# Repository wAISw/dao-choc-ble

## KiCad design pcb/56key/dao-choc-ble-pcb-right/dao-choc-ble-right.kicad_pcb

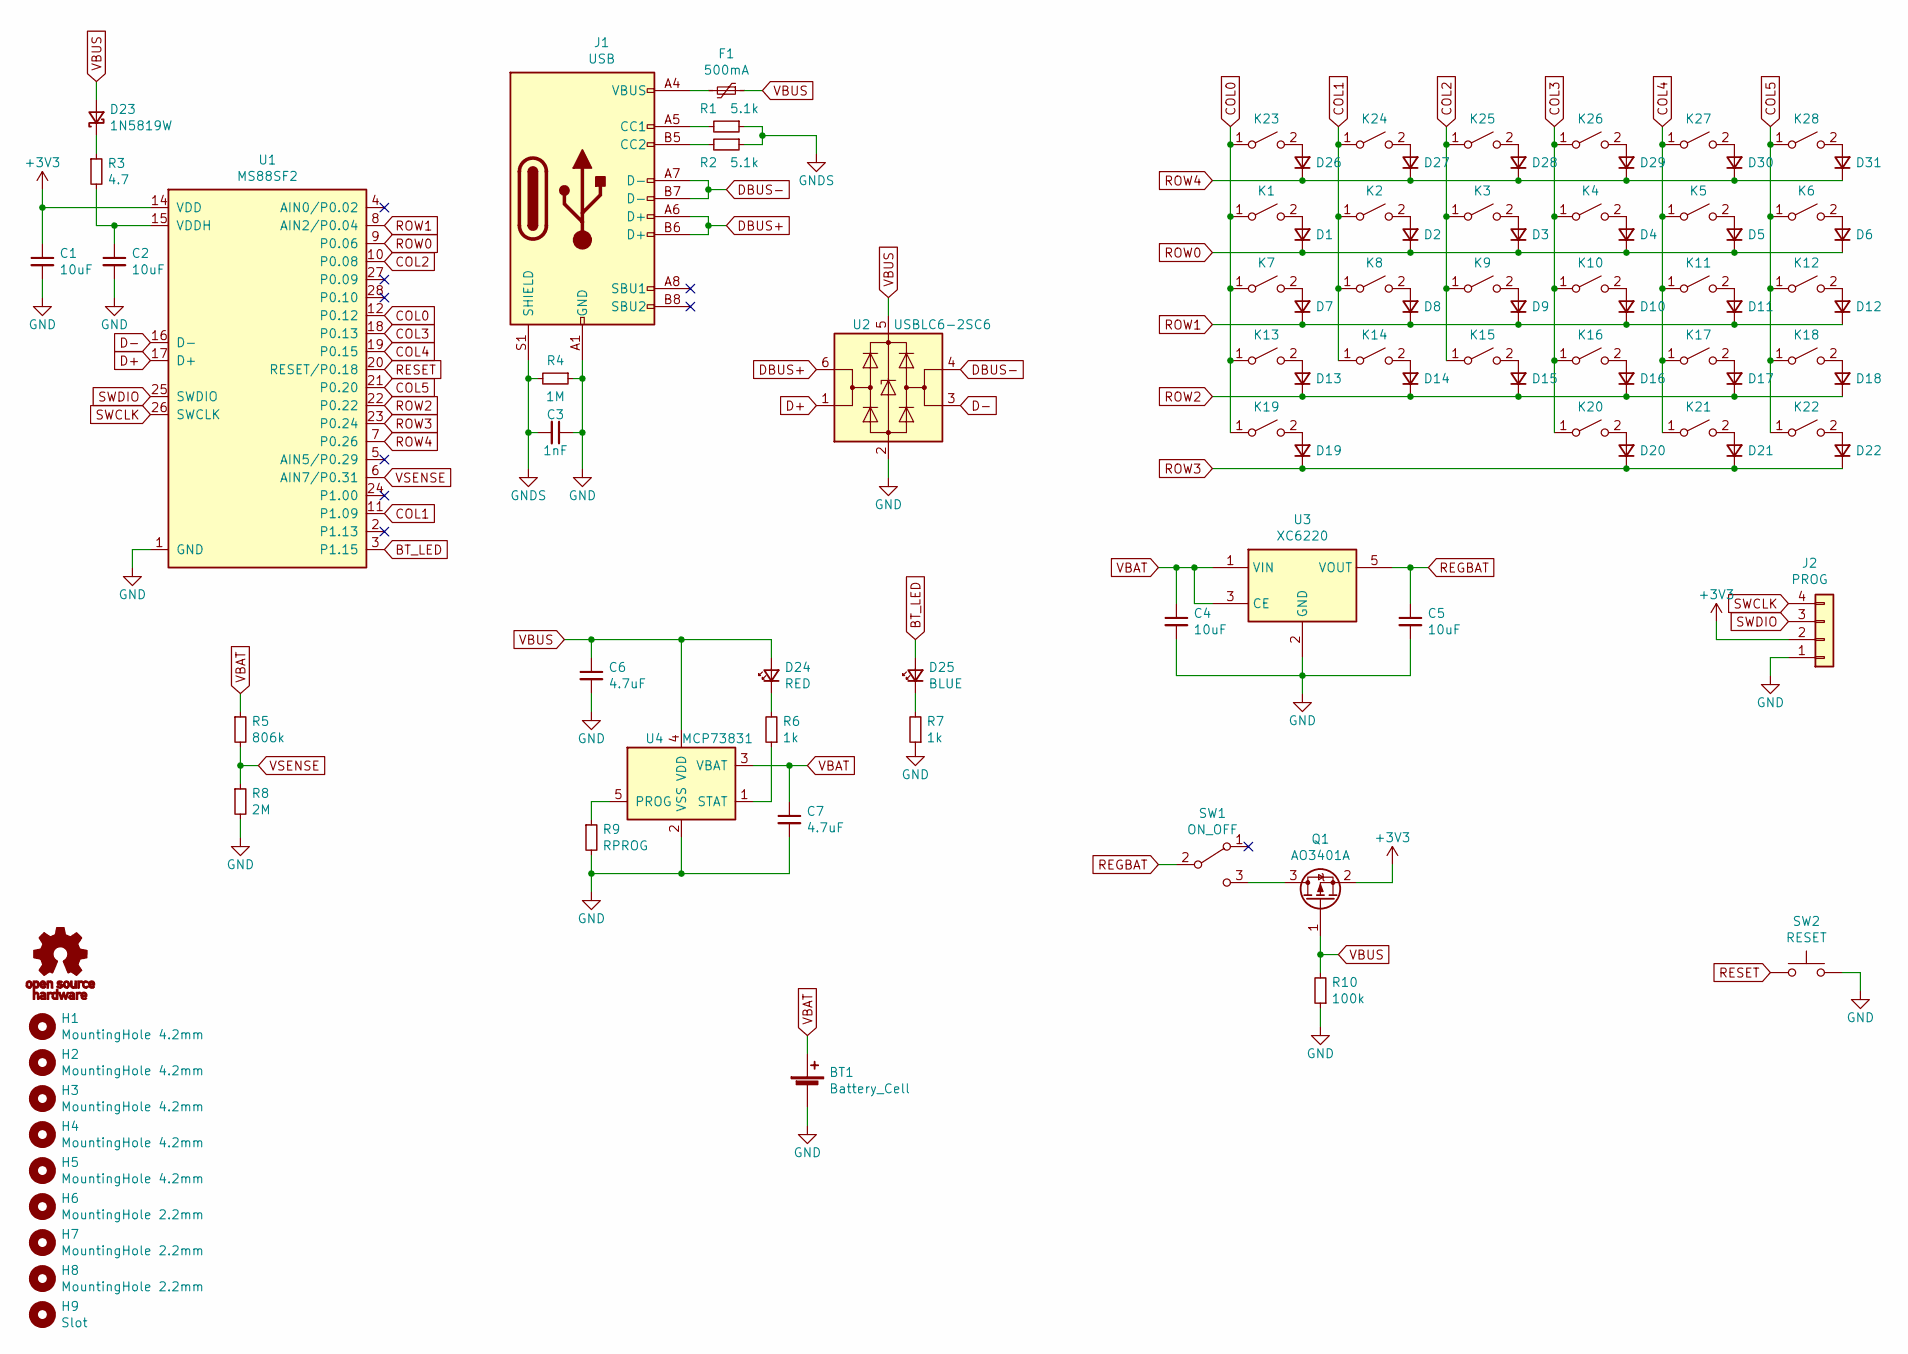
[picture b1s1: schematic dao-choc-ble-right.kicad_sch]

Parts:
BT1: Battery_Cell; Battery
C1, C2, C4, C5: 10uF; C_0603_1608Metric; LCSC C19702
C3: 1nF; C_0603_1608Metric; LCSC C1588
C6, C7: 4.7uF; C_0603_1608Metric; LCSC C19666
D1, D2, D3, D4, D5, D6, D7, D8, D9, D10, D11, D12, D13, D14, D15, D16, D17, D18, D19, D20, D21, D22, D26, D27, D28, D29, D30, D31: 1N4148WS; D_SOD-323; LCSC C57759
D23: 1N5819W; D_SOD-123; LCSC C169540
D24: RED; LED_0603_1608Metric; LCSC C2286
D25: BLUE; LED_0603_1608Metric; LCSC C72041
F1: 500mA; Fuse_1206_3216Metric; LCSC C355568
H1, H2, H3, H4, H5: MountingHole 4.2mm; Hole_4.2mm
H6, H7, H8: MountingHole 2.2mm; Hole_2.2mm
H9: Slot
J1: USB; USB-C_C168688; LCSC C168688
J2: PROG
K1, K2, K3, K4, K5, K6, K7, K8, K9, K10, K11, K12, K13, K14, K15, K16, K17, K18, K19, K20, K21, K22, K23, K24, K25, K26, K27, K28: KEY_SWITCH; Kailh_PG1350_hotswap
LOGO1: OSHW-logo
Q1: AO3401A; SOT-23; LCSC C15127
R1, R2: 5.1k; R_0603_1608Metric; LCSC C23186
R3: 4.7; R_0603_1608Metric; LCSC C23164
R4: 1M; R_0603_1608Metric; LCSC C22935
R5: 806k; R_0603_1608Metric; LCSC C103828
R6, R7: 1k; R_0603_1608Metric; LCSC C21190
R8: 2M; R_0603_1608Metric; LCSC C22976
R9: RPROG; R_0603_1608Metric; LCSC C22978
R10: 100k; R_0603_1608Metric; LCSC C25803
SW1: ON_OFF; MSK-12C02; LCSC C431541
SW2: RESET; TS-1086E; LCSC C455276
U1: MS88SF2; MINEW_MS88SF2
U2: USBLC6-2SC6; SOT-23-6; LCSC C558442
U3: XC6220; SOT-23-5; LCSC C86534
U4: MCP73831; SOT-23-5; LCSC C14879

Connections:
+3V3: C1.1, J2.2, Q1.2 (S), U1.14 (VDD)
BT_LED: D25.2 (A), U1.3 (P1.15)
COL0: K1.1 (A), K7.1 (A), K13.1 (A), K19.1 (A), K23.1 (A), U1.12 (P0.12)
COL1: K2.1 (A), K8.1 (A), K14.1 (A), K24.1 (A), U1.11 (P1.09)
COL2: K3.1 (A), K9.1 (A), K15.1 (A), K25.1 (A), U1.10 (P0.08)
COL3: K4.1 (A), K10.1 (A), K16.1 (A), K20.1 (A), K26.1 (A), U1.18 (P0.13)
COL4: K5.1 (A), K11.1 (A), K17.1 (A), K21.1 (A), K27.1 (A), U1.19 (P0.15)
COL5: K6.1 (A), K12.1 (A), K18.1 (A), K22.1 (A), K28.1 (A), U1.21 (P0.20)
D+: U1.17 (D+), U2.1 (I/O1)
D-: U1.16 (D-), U2.3 (I/O2)
DBUS+: J1.A6 (D+), J1.B6 (D+), U2.6 (I/O1)
DBUS-: J1.A7 (D-), J1.B7 (D-), U2.4 (I/O2)
GND: BT1.2 (-), C1.2, C2.2, C3.1, C4.2, C5.2, C6.2, C7.2, J1.A1 (GND), J1.A12 (GND), J1.B1 (GND), J1.B12 (GND), J2.1, R4.1, R7.1, R8.2, R9.2, R10.1, SW2.2, U1.1 (GND), U1.13 (GND), U2.2 (GND), U3.2 (GND), U4.2 (VSS)
GNDS: C3.2, J1.S1 (SHIELD), R1.1, R2.1, R4.2
unnamed: C2.1, R3.2, U1.15 (VDDH)
unnamed: D1.2 (A), K1.2 (B)
unnamed: D2.2 (A), K2.2 (B)
unnamed: D3.2 (A), K3.2 (B)
unnamed: D4.2 (A), K4.2 (B)
unnamed: D5.2 (A), K5.2 (B)
unnamed: D6.2 (A), K6.2 (B)
unnamed: D7.2 (A), K7.2 (B)
unnamed: D8.2 (A), K8.2 (B)
unnamed: D9.2 (A), K9.2 (B)
unnamed: D10.2 (A), K10.2 (B)
unnamed: D11.2 (A), K11.2 (B)
unnamed: D12.2 (A), K12.2 (B)
unnamed: D13.2 (A), K13.2 (B)
unnamed: D14.2 (A), K14.2 (B)
unnamed: D15.2 (A), K15.2 (B)
unnamed: D16.2 (A), K16.2 (B)
unnamed: D17.2 (A), K17.2 (B)
unnamed: D18.2 (A), K18.2 (B)
unnamed: D19.2 (A), K19.2 (B)
unnamed: D20.2 (A), K20.2 (B)
unnamed: D21.2 (A), K21.2 (B)
unnamed: D22.2 (A), K22.2 (B)
unnamed: D23.1 (K), R3.1
unnamed: D24.1 (K), R6.2
unnamed: D25.1 (K), R7.2
unnamed: F1.2, J1.A4 (VBUS), J1.A9 (VBUS), J1.B4 (VBUS), J1.B9 (VBUS)
unnamed: J1.A5 (CC1), R1.2
unnamed: J1.B5 (CC2), R2.2
unnamed: D26.2 (A), K23.2 (B)
unnamed: D27.2 (A), K24.2 (B)
unnamed: D28.2 (A), K25.2 (B)
unnamed: D29.2 (A), K26.2 (B)
unnamed: D30.2 (A), K27.2 (B)
unnamed: D31.2 (A), K28.2 (B)
unnamed: Q1.3 (D), SW1.3 (C)
unnamed: R6.1, U4.1 (STAT)
unnamed: R9.1, U4.5 (PROG)
REGBAT: C5.1, SW1.2 (B), U3.5 (VOUT)
RESET: SW2.1, U1.20 (RESET/P0.18)
ROW0: D1.1 (K), D2.1 (K), D3.1 (K), D4.1 (K), D5.1 (K), D6.1 (K), U1.9 (P0.06)
ROW1: D7.1 (K), D8.1 (K), D9.1 (K), D10.1 (K), D11.1 (K), D12.1 (K), U1.8 (AIN2/P0.04)
ROW2: D13.1 (K), D14.1 (K), D15.1 (K), D16.1 (K), D17.1 (K), D18.1 (K), U1.22 (P0.22)
ROW3: D19.1 (K), D20.1 (K), D21.1 (K), D22.1 (K), U1.23 (P0.24)
ROW4: D26.1 (K), D27.1 (K), D28.1 (K), D29.1 (K), D30.1 (K), D31.1 (K), U1.7 (P0.26)
SWCLK: J2.4, U1.26 (SWCLK)
SWDIO: J2.3, U1.25 (SWDIO)
VBAT: BT1.1 (+), C4.1, C7.1, R5.1, U3.1 (VIN), U3.3 (CE), U4.3 (VBAT)
VBUS: C6.1, D23.2 (A), D24.2 (A), F1.1, Q1.1 (G), R10.2, U2.5 (VBUS), U4.4 (VDD)
VSENSE: R5.2, R8.1, U1.6 (AIN7/P0.31)

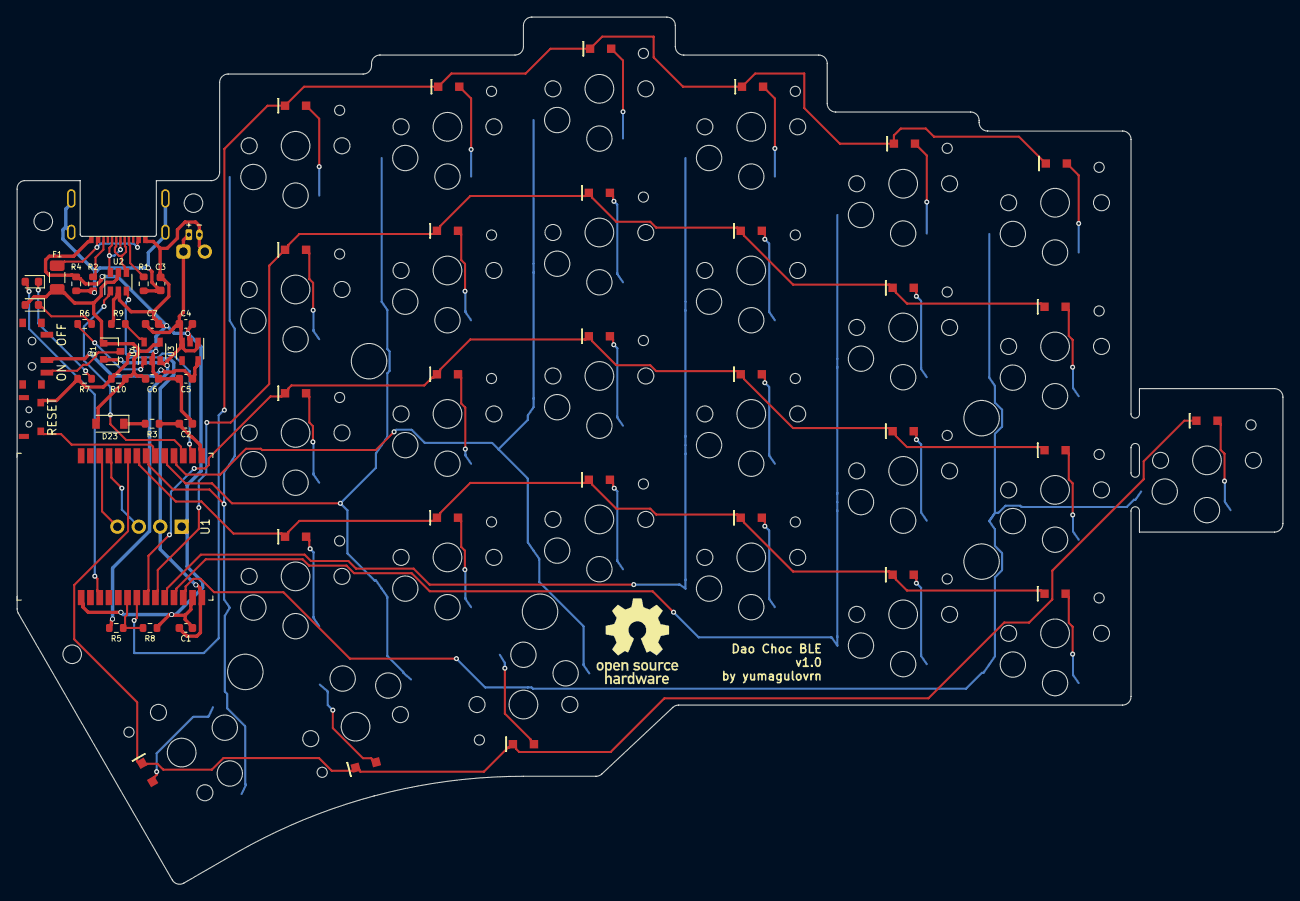
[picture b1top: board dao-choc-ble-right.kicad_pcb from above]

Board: 2 copper layers, 150.0 x 102.8 mm, 97 parts (1 on the bottom side), 64 nets.

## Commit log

2022-12-01 First iteration of 56 key left side.
2022-12-05 Fixed errors
2022-12-06 Fixed errors.
2022-12-07 Updated right side.
2022-12-10 Created top plate.

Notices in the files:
pcb/56key/dao-choc-ble-pcb-right/dao-choc-ble-right.kicad_pcb:
Copyright (c) 2021
Licensed under CERN-OHL-P v2
